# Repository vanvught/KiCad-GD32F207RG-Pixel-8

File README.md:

# KiCad GD32F207RG Pixel 8-ports x 4 Universes

Firmware [https://github.com/vanvught/GD32F207RG-DMX512-RDM](https://github.com/vanvught/GD32F207RG-DMX512-RDM)

More information [https://www.gd32-dmx.org/pixel.html](https://www.gd32-dmx.org/pixel.html)

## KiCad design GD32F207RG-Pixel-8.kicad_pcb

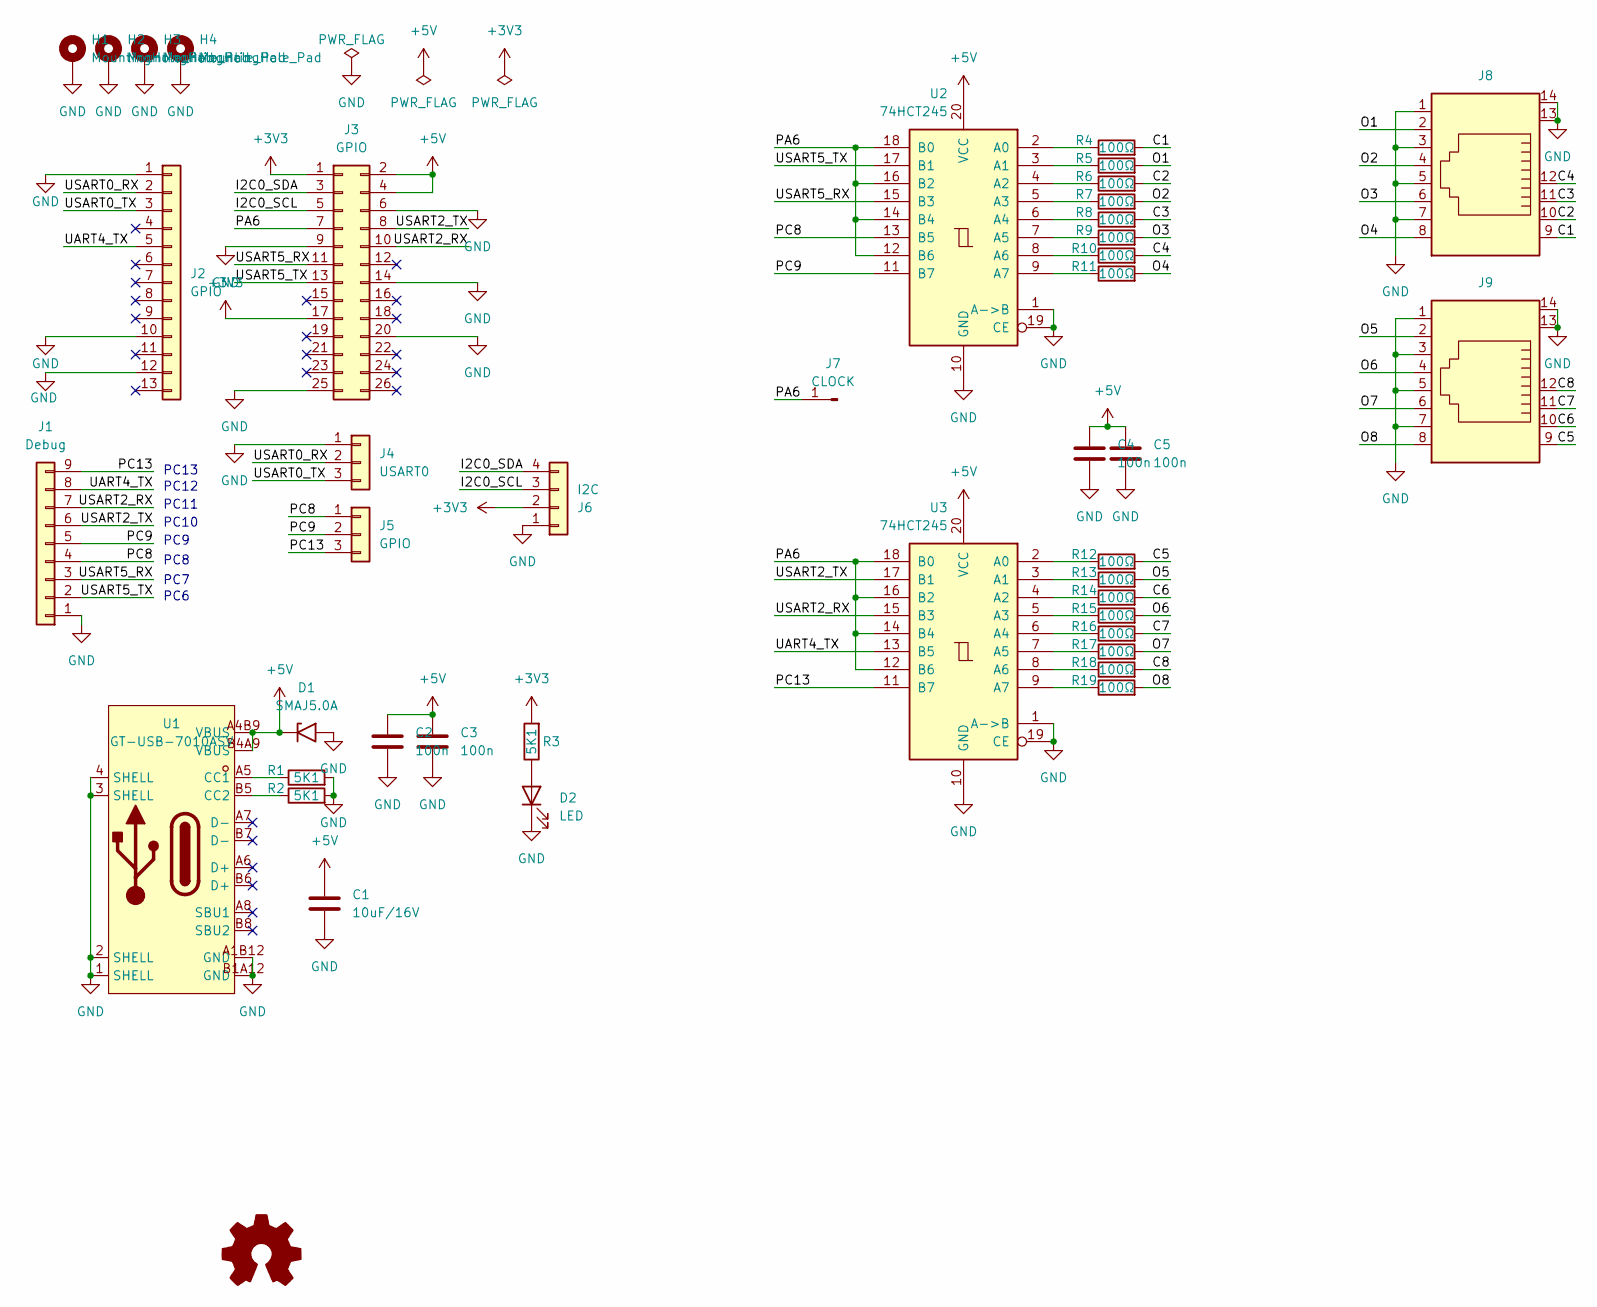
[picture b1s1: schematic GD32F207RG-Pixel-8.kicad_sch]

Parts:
C1: 10uF/16V; C_0603_1608Metric; LCSC Part C19702
C2, C3, C4, C5: 100n; C_0603_1608Metric; LCSC Part C14663
D1: SMAJ5.0A; D_SMA; LCSC Part C113952
D2: LED; LED_0805_2012Metric; LCSC Part C2297
H1, H2, H3, H4: MountingHole_Pad; MountingHole_2.7mm_M2.5_Pad
J1: Debug; PinHeader_1x09_P2.54mm_Vertical
J2: GPIO; PinSocket_1x13_P2.54mm_Vertical
J3: GPIO; PinSocket_2x13_P2.54mm_Vertical
J4: USART0; PinHeader_1x03_P2.54mm_Vertical
J5: GPIO; PinSocket_1x03_P2.54mm_Vertical
J6: I2C; PinHeader_1x04_P2.54mm_Vertical
J7: CLOCK; PinHeader_1x01_P2.54mm_Vertical
J8, J9: RJ45-with-additional-row
R1, R2, R3: 5K1; R_0603_1608Metric; LCSC Part C23186
R4, R5, R6, R7, R8, R9, R10, R11, R12, R13, R14, R15, R16, R17, R18, R19: 100Ω; R_0603_1608Metric; LCSC Part C22775
SYM1: Logo_Open_Hardware_Small; OSHW-Logo_7.5x8mm_SilkScreen
U1: GT-USB-7010ASV; USB-C-SMD_G-SWITCH_GT-USB-7010ASV; MPN GT-USB-7010ASV; LCSC Part C2988369
U2, U3: 74HCT245; SOIC-20W_7.5x12.8mm_P1.27mm; LCSC Part C5979

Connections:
+3V3: J3.1, J3.17, J6.2, R3.2
+5V: C1.1, C2.1, C3.1, C4.1, C5.1, D1.1 (A1), J3.2, J3.4, U1.A4B9 (VBUS), U1.B4A9 (VBUS), U2.20 (VCC), U3.20 (VCC)
/C1: J8.9, R4.2
/C2: J8.10, R6.2
/C3: J8.11, R8.2
/C4: J8.12, R10.2
/C5: J9.9, R12.2
/C6: J9.10, R14.2
/C7: J9.11, R16.2
/C8: J9.12, R18.2
/I2C0_SCL: J3.5, J6.3
/I2C0_SDA: J3.3, J6.4
/O1: J8.2, R5.2
/O2: J8.4, R7.2
/O3: J8.6, R9.2
/O4: J8.8, R11.2
/O5: J9.2, R13.2
/O6: J9.4, R15.2
/O7: J9.6, R17.2
/O8: J9.8, R19.2
/PA6: J3.7, J7.1 (Pin_1_1), U2.12 (B6), U2.14 (B4), U2.16 (B2), U2.18 (B0), U3.12 (B6), U3.14 (B4), U3.16 (B2), U3.18 (B0)
/PC8: J1.4, J5.1, U2.13 (B5)
/PC9: J1.5, J5.2, U2.11 (B7)
/PC13: J1.9, J5.3, U3.11 (B7)
/UART4_TX: J1.8, J2.5, U3.13 (B5)
/USART0_RX: J2.2, J4.2
/USART0_TX: J2.3, J4.3
/USART2_RX: J1.7, J3.10, U3.15 (B3)
/USART2_TX: J1.6, J3.8, U3.17 (B1)
/USART5_RX: J1.3, J3.11, U2.15 (B3)
/USART5_TX: J1.2, J3.13, U2.17 (B1)
GND: C1.2, C2.2, C3.2, C4.2, C5.2, D1.2 (A2), D2.1 (K), H1.1 (1_1), H2.1 (1_1), H3.1 (1_1), H4.1 (1_1), J1.1, J2.1, J2.10, J2.12, J3.6, J3.9, J3.14, J3.20, J3.25, J4.1, J6.1, J8.1, J8.3, J8.5, J8.7, J8.13, J8.14, J9.1, J9.3, J9.5, J9.7, J9.13, J9.14, R1.2, R2.2, U1.1 (SHELL), U1.2 (SHELL), U1.3 (SHELL), U1.4 (SHELL), U1.A1B12 (GND), U1.B1A12 (GND), U2.1 (A->B), U2.10 (GND), U2.19 (CE), U3.1 (A->B), U3.10 (GND), U3.19 (CE)
unnamed: D2.2 (A), R3.1
unnamed: R1.1, U1.A5 (CC1)
unnamed: R2.1, U1.B5 (CC2)
unnamed: R4.1, U2.2 (A0)
unnamed: R5.1, U2.3 (A1)
unnamed: R6.1, U2.4 (A2)
unnamed: R7.1, U2.5 (A3)
unnamed: R8.1, U2.6 (A4)
unnamed: R9.1, U2.7 (A5)
unnamed: R10.1, U2.8 (A6)
unnamed: R11.1, U2.9 (A7)
unnamed: R12.1, U3.2 (A0)
unnamed: R13.1, U3.3 (A1)
unnamed: R14.1, U3.4 (A2)
unnamed: R15.1, U3.5 (A3)
unnamed: R16.1, U3.6 (A4)
unnamed: R17.1, U3.7 (A5)
unnamed: R18.1, U3.8 (A6)
unnamed: R19.1, U3.9 (A7)

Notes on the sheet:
PC11
PC12
PC13
PC9
PC6
PC8
PC10
PC7

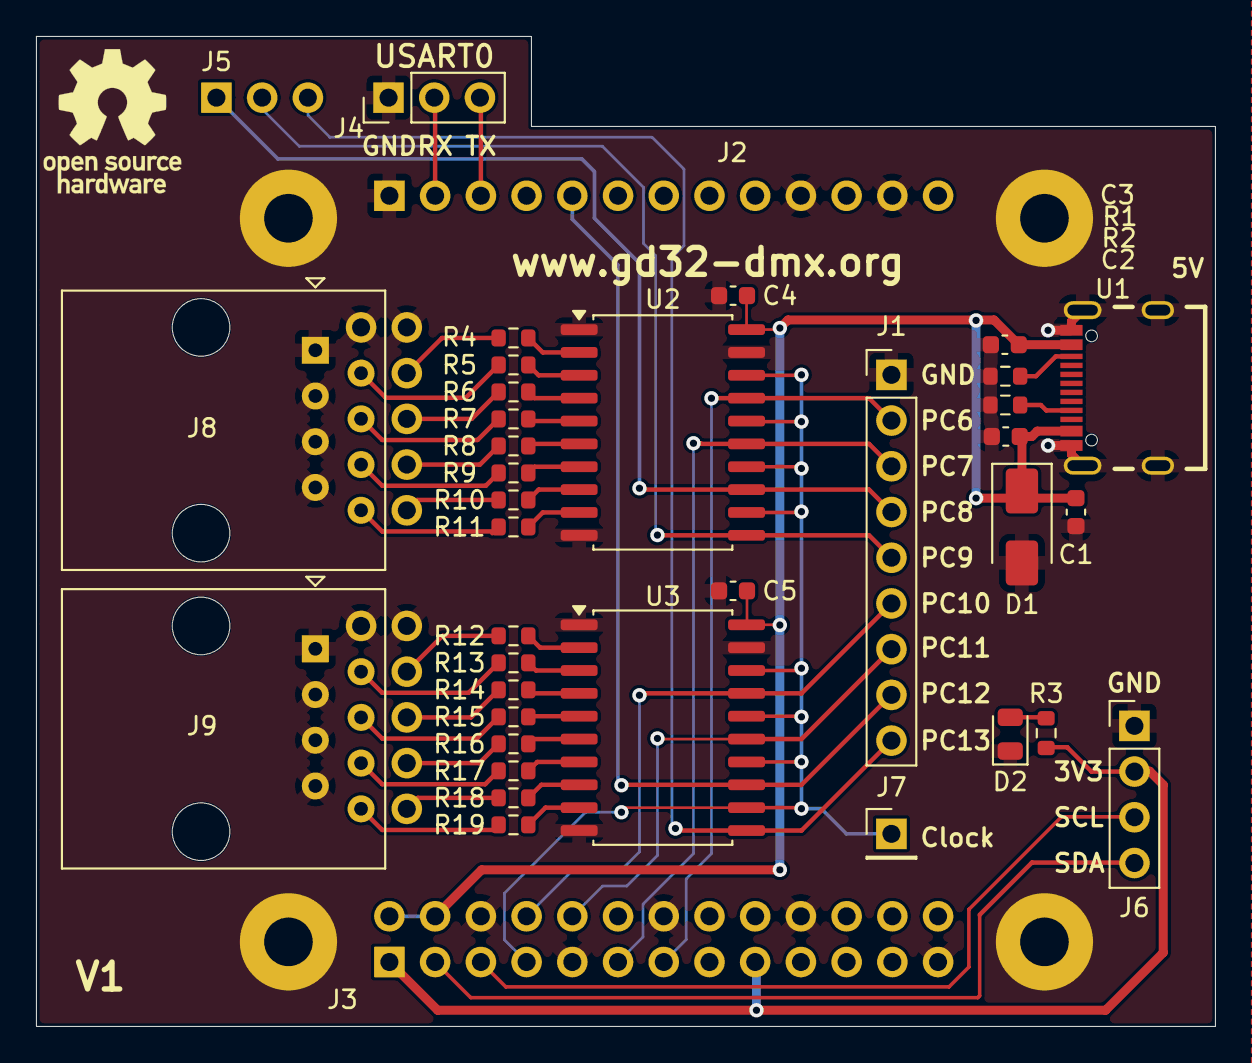
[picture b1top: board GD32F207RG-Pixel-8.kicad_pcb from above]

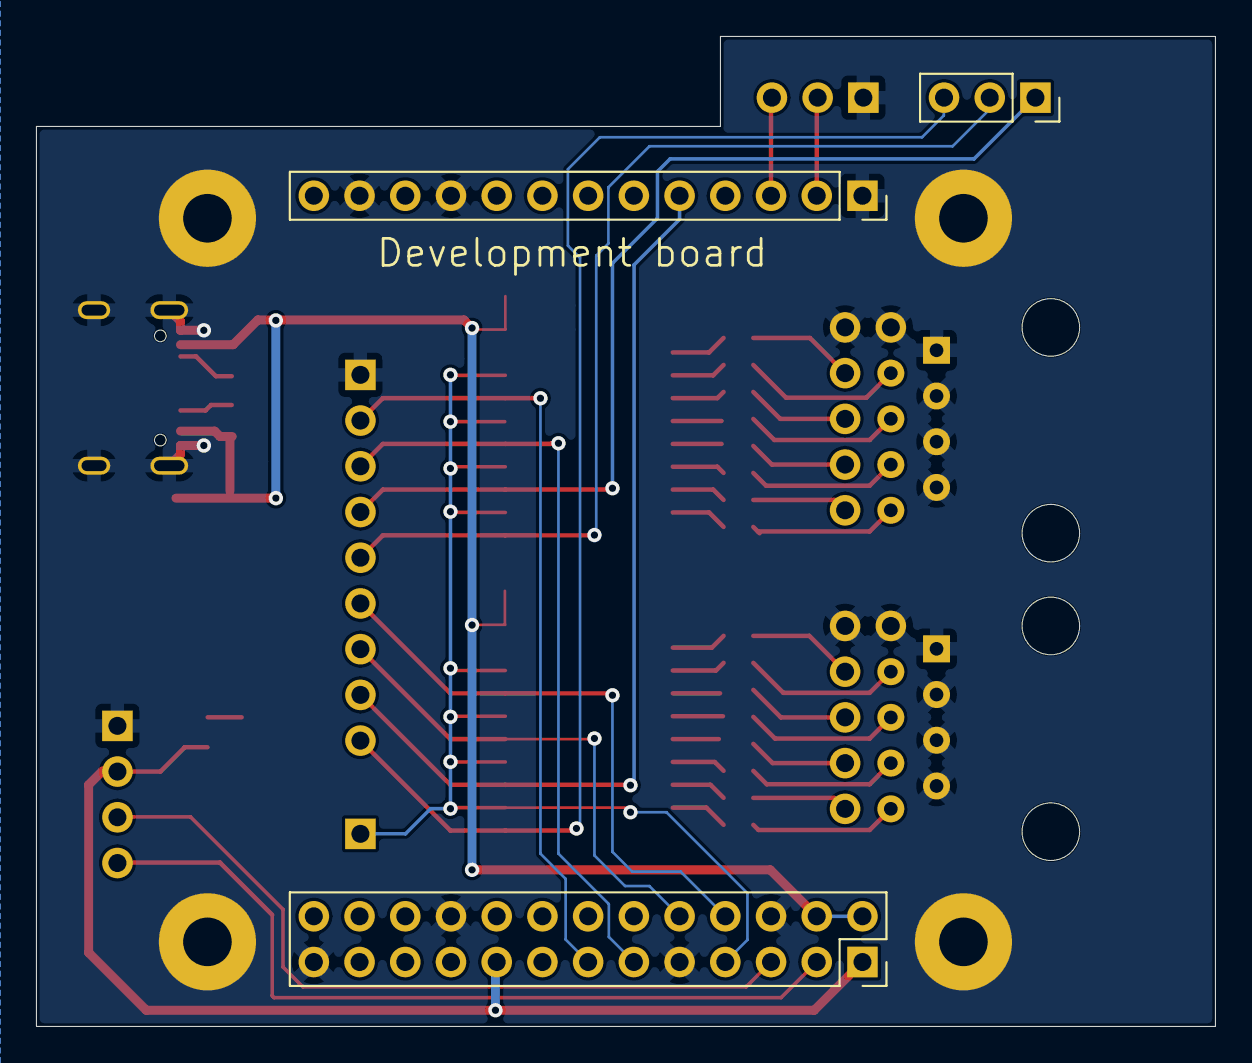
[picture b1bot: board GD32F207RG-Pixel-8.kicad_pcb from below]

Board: 2 copper layers, 65.5 x 55.0 mm, 43 parts (3 on the bottom side), 51 nets.

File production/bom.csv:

Designator,Footprint,Quantity,Value,LCSC Part #
C1,0603,1,10uF/16V,C19702
"C2, C3, C4, C5",0603,4,100n,C14663
D1,D_SMA,1,SMAJ5.0A,C113952
D2,0805,1,LED,C2297
"R1, R2, R3",0603,3,5K1,C23186
"R10, R11, R12, R13, R14, R15, R16, R17, R18, R19, R4, R5, R6, R7, R8, R9",0603,16,100Ω,C22775
U1,USB-C-SMD_G-SWITCH_GT-USB-7010ASV,1,GT-USB-7010ASV,C2988369
"U2, U3",SOIC-20W_7.5x12.8mm_P1.27mm,2,74HCT245,C5979
